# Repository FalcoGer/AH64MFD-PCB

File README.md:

# AH64MFD-PCB
PCB for an AH64 MFD

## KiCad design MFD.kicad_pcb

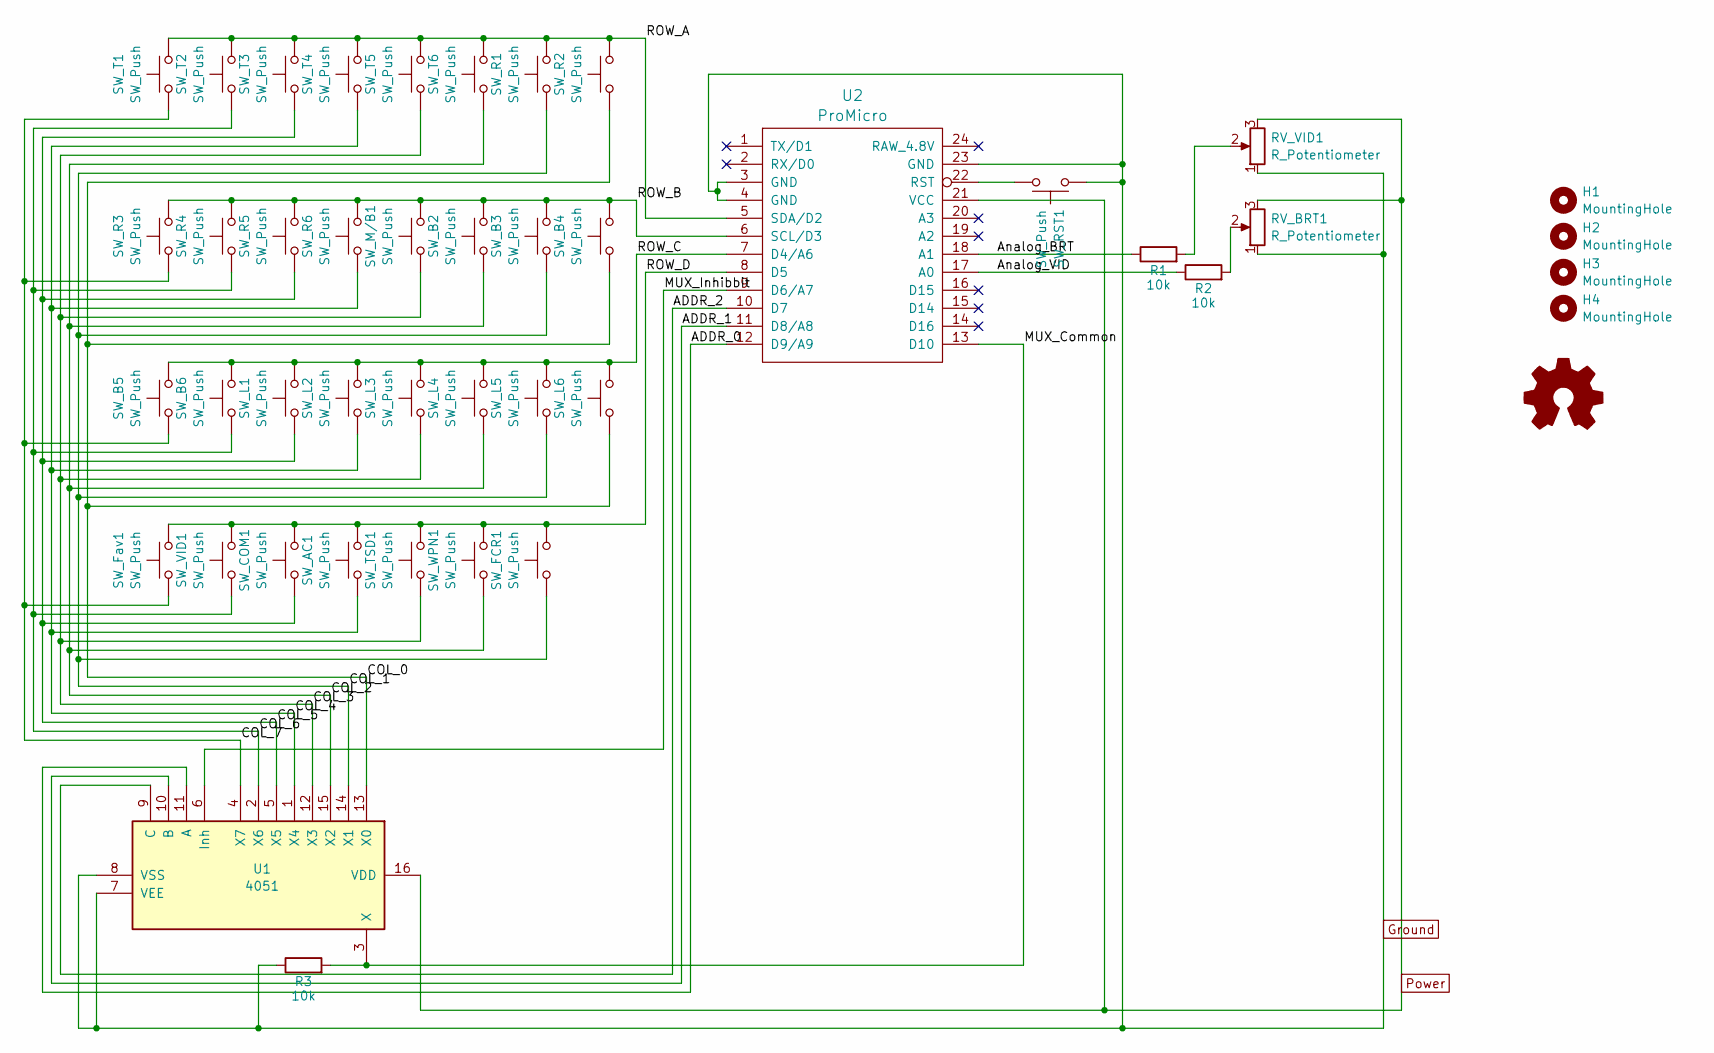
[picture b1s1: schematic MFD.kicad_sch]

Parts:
H1, H2, H3, H4: MountingHole; MountingHole_5.3mm_M5
R1, R2, R3: 10k; R_Axial_DIN0204_L3.6mm_D1.6mm_P5.08mm_Horizontal
RV_BRT1: R_Potentiometer; LAP_Electronics_Potentiometer_Pads_With_Holes_Tight
RV_VID1: R_Potentiometer; LAP_Electronics_Potentiometer_Pads_With_Holes_Tight
SW_AC1: SW_Push; SW_PUSH_6mm_H5mm
SW_B2, SW_B3, SW_B4, SW_B5, SW_B6: SW_Push; SW_PUSH_6mm_H5mm
SW_COM1: SW_Push; SW_PUSH_6mm_H5mm
SW_FCR1: SW_Push; SW_PUSH_6mm_H5mm
SW_Fav1: SW_Push; SW_PUSH_6mm_H5mm
SW_L1, SW_L2, SW_L3, SW_L4, SW_L5, SW_L6: SW_Push; SW_PUSH_6mm_H5mm
SW_M/B1: SW_Push; SW_PUSH_6mm_H5mm
SW_R1, SW_R2, SW_R3, SW_R4, SW_R5, SW_R6: SW_Push; SW_PUSH_6mm_H5mm
SW_RST1: SW_Push; SW_PUSH_6mm_H5mm
SW_T1, SW_T2, SW_T3, SW_T4, SW_T5, SW_T6: SW_Push; SW_PUSH_6mm_H5mm
SW_TSD1: SW_Push; SW_PUSH_6mm_H5mm
SW_VID1: SW_Push; SW_PUSH_6mm_H5mm
SW_WPN1: SW_Push; SW_PUSH_6mm_H5mm
SYM1: Logo_Open_Hardware_Small; OSHW-Logo2_7.3x6mm_SilkScreen
U1: 4051; DIP-16_W7.62mm
U2: ProMicro

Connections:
/ADDR_0: U1.11 (A), U2.12 (D9/A9)
/ADDR_1: U1.10 (B), U2.11 (D8/A8)
/ADDR_2: U1.9 (C), U2.10 (D7)
/Analog_BRT: R1.1, U2.18 (A1)
/Analog_VID: R2.1, U2.17 (A0)
/COL_0: SW_B4.1, SW_L6.1, SW_R2.1, U1.13 (X0)
/COL_1: SW_B3.1, SW_FCR1.1, SW_L5.1, SW_R1.1, U1.14 (X1)
/COL_2: SW_B2.1, SW_L4.1, SW_T6.1, SW_WPN1.1, U1.15 (X2)
/COL_3: SW_L3.1, SW_M/B1.1, SW_T5.1, SW_TSD1.1, U1.12 (X3)
/COL_4: SW_AC1.1, SW_L2.1, SW_R6.1, SW_T4.1, U1.1 (X4)
/COL_5: SW_COM1.1, SW_L1.1, SW_R5.1, SW_T3.1, U1.5 (X5)
/COL_6: SW_B6.1, SW_R4.1, SW_T2.1, SW_VID1.1, U1.2 (X6)
/COL_7: SW_B5.1, SW_Fav1.1, SW_R3.1, SW_T1.1, U1.4 (X7)
/MUX_Common: R3.2, U1.3 (X), U2.13 (D10)
/MUX_Inhibbit: U1.6 (Inh), U2.9 (D6/A7)
/ROW_A: SW_R1.2, SW_R2.2, SW_T1.2, SW_T2.2, SW_T3.2, SW_T4.2, SW_T5.2, SW_T6.2, U2.5 (SDA/D2)
/ROW_B: SW_B2.2, SW_B3.2, SW_B4.2, SW_M/B1.2, SW_R3.2, SW_R4.2, SW_R5.2, SW_R6.2, U2.6 (SCL/D3)
/ROW_C: SW_B5.2, SW_B6.2, SW_L1.2, SW_L2.2, SW_L3.2, SW_L4.2, SW_L5.2, SW_L6.2, U2.7 (D4/A6)
/ROW_D: SW_AC1.2, SW_COM1.2, SW_FCR1.2, SW_Fav1.2, SW_TSD1.2, SW_VID1.2, SW_WPN1.2, U2.8 (D5)
Ground: R3.1, RV_BRT1.1, RV_VID1.1, SW_RST1.1, U1.7 (VEE), U1.8 (VSS), U2.3 (GND), U2.4 (GND), U2.23 (GND)
unnamed: R1.2, RV_VID1.2
unnamed: R2.2, RV_BRT1.2
unnamed: SW_RST1.2, U2.22 (RST)
Power: RV_BRT1.3, RV_VID1.3, U1.16 (VDD), U2.21 (VCC)

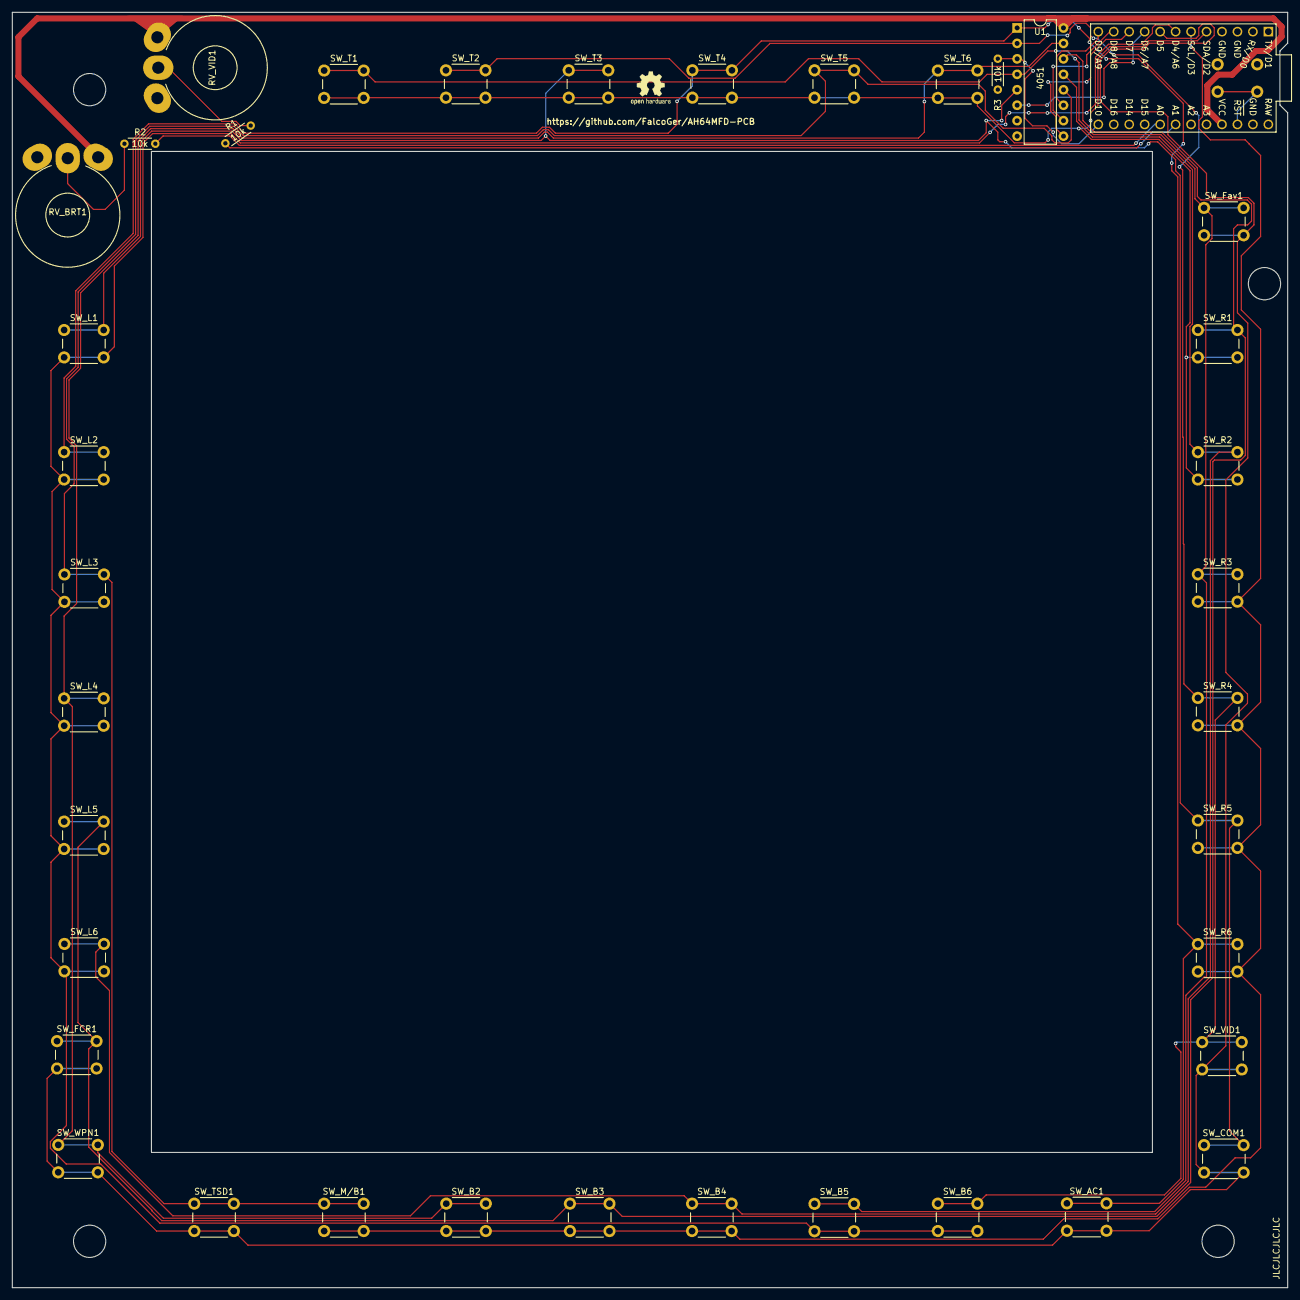
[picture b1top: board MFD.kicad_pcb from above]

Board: 2 copper layers, 209.6 x 209.6 mm, 44 parts (1 on the bottom side), 24 nets.

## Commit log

2024-02-15 Add everything
2024-02-15 Update gitignore
2024-02-15 Adds OpenHardware Logo and GitHub link
2024-02-15 Rename job zip
2024-02-15 rerouted some tracks to use less vias.
2024-02-15 Update README.md
    adds image to readme.
2024-02-15 Adds mounting holes to schematic\nReroutes some tracks
2024-02-15 Ground plane over everything Rerouted some tracks, less vias
2024-02-15 Cleanup tracks
2024-02-17 Adds more dimensions
2024-02-17 re-adds open hardware silkscreen adds open hardware symbol to schematic adds net names
